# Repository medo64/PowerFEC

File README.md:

Power Framework Expansion Card
==============================

Non-isolated 5V output with a 500 mA current limit.

## Pinout

To connect to this board, one has to use a 2-pin JST XH connector. The following
table represents the pinout, pin 1 being on the left as looking into the
expansion card.

| # | Ref   | Description                     |
|--:|:-----:|---------------------------------|
| 1 | GND   | Ground connection               |
| 2 | 5V    | Positive voltage                |

## LEDs

Left LED signals if input is powered. It is expected to be on at all times.

Right LED signals if output is powered and there are no faults. It will turn off
if there is an over-current state (typically at around `525 mA`).

## Commands

Each char is a separate command. If it is recognized, output will be tilde
character (`~`), original command, and `CR``LF`.

| Char | Description                                                   |
|------|---------------------------------------------------------------|
| `0`  | No smoothing for voltage and current                          |
| `1`  | Voltage and current read are smoothed over 2 readings         |
| `2`  | Voltage and current read are smoothed over 4 readings         |
| `3`  | Voltage and current read are smoothed over 8 readings         |
| `4`  | Voltage and current read are smoothed over 16 readings        |
| `5`  | Voltage and current read are smoothed over 32 readings        |
| `6`  | Voltage and current read are smoothed over 64 readings        |
| `7`  | Voltage and current read are smoothed over 128 readings       |
| `8`  | Voltage and current read are smoothed over 256 readings       |
| `9`  | Voltage and current read are smoothed over 512 readings       |
| `d`  | Disable output                                                |
| `D`  | Disable output and allow saving for startup                   |
| `e`  | Enable output                                                 |
| `E`  | Enable output and allow saving for startup                    |
| `S`  | Saves current settings                                        |

Any command state that can be saved permanently (e.g. `E`) needs to be followed
by `S` command in order to be saved.

---
*You can check my blog and other projects at [www.medo64.com](https://www.medo64.com/electronics/).*

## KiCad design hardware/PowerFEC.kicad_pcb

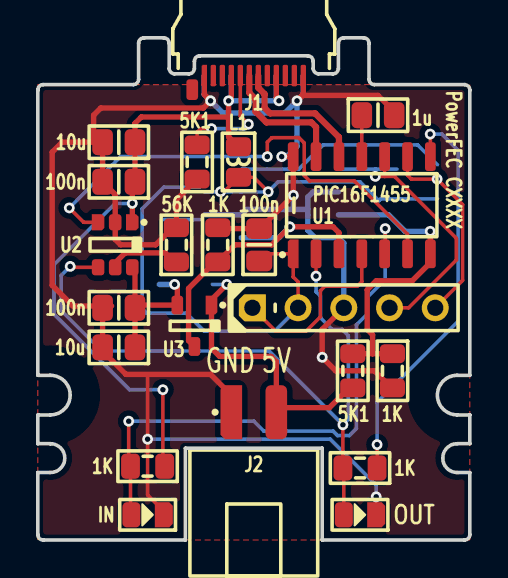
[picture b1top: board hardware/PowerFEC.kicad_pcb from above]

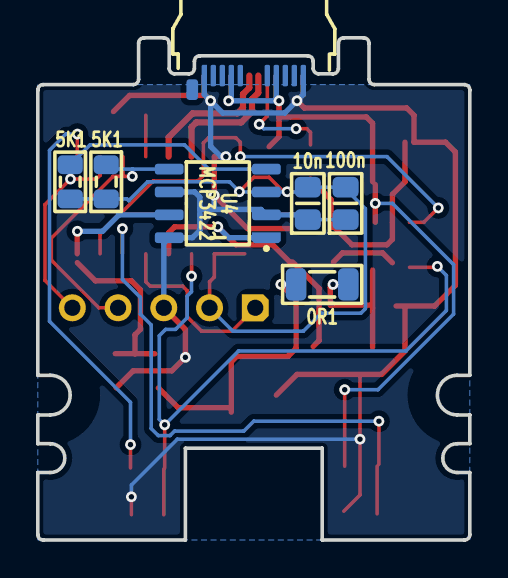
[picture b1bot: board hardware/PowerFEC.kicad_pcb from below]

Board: 2 copper layers, 24.0 x 27.9 mm, 28 parts (6 on the bottom side), 19 nets.

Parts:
C1: 10n; C (0805)
C2, C3, C4, C5: 100n; C (0805)
C6: 1u; C (0805)
C7, C8: 10u; C (0805)
DS1: IN; DS (0805)
DS2: OUT; DS (0805)
ICSP: Microchip PIC; ICSP PIC Pogo (5w)
J1: 105444-0001; J USB C 3.2 Edge (24w)
J2: B2B-XH-A; J JST XH Edge [POWER] (2w)
L1: 1u; L (0805)
R1: 0R1; R (1206)
R2, R3, R4, R5: 1K; R (0805)
R6, R7, R8, R9: 5K1; R (0805)
R10: 56K; R (0805)
U1: PIC16F1455; U Micro [PIC16F1455] (SOIC-14)
U2: AP22652; U LoadSwitch Adjustable [AP22652AW6-7] (SOT23-6)
U3: ZXCT1009; U Current Monitor [ZXCT1009] (SOT23-3)
U4: MCP3422; U ADC 18bit 2ch [MCP3422] (SOIC-8)

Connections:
5V: C1.1, C4.1, C5.1, ICSP.2, L1.2, R8.1, R9.1, U1.1, U4.3
A_CC: J1.A5, R6.2
GND: C1.2, C2.2, C3.2, C4.2, C5.2, C6.2, C7.2, C8.2, DS1.1, DS2.1, ICSP.3, J1.A1, J1.A12, J1.B01, J1.B12, J2.1, R2.2, R5.2, R6.1, R10.2, U1.14, U2.2, U4.2, U4.6, U4.8
ICSP_CLK/SDA: ICSP.5, R9.2, U1.9, U4.4
ICSP_DAT/SCL: ICSP.4, R8.2, U1.10, U4.5
ICSP_VPP: ICSP.1, U1.4
ILIM: R10.1, U2.5
Iadc: R2.1, U1.3, U3.3, U4.1
LED_IN: DS1.2, R3.2, U1.5
LED_OUT_HIGH: R4.1, U1.8
POWER_EN: U1.6, U2.3
POWER_FAULT: DS2.2, R4.2, U1.2, U2.4
USB_DM: J1.A7, U1.12
USB_DP: J1.A6, U1.13
V33: C6.1, U1.11
Vadc: R5.1, R7.2, U1.7, U4.7
Vin: C2.1, C7.1, J1.A4, J1.A9, J1.B04, J1.B09, L1.1, R3.1, U2.1
Vout: J2.2, R1.2, R7.1, U3.1
Vsw: C3.1, C8.1, R1.1, U2.6, U3.2

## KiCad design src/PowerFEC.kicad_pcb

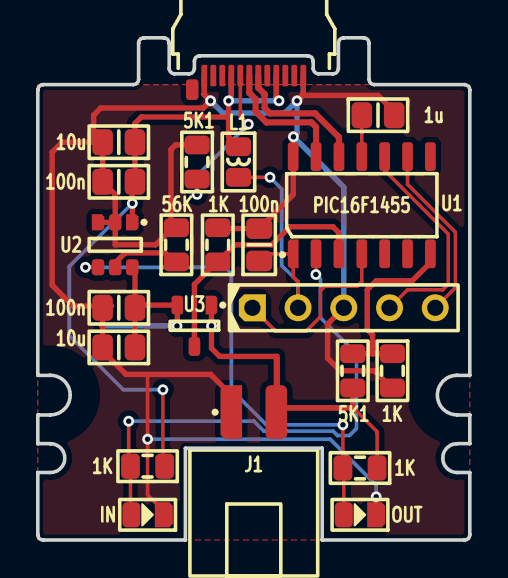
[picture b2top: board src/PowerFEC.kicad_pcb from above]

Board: 2 copper layers, 24.0 x 27.9 mm, 23 parts (1 on the bottom side), 17 nets.

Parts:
C1, C2, C3: 100n; C (0805)
C4: 1u; C (0805)
C5, C6: 10u; C (0805)
DS1: IN; DS (0805)
DS2: OUT; DS (0805)
ICSP: Microchip PIC; ICSP PIC Pogo (5w)
J1: B2B-XH-A; J JST XH Edge [POWER] (2w)
L1: 1u; L (0805)
P1: 105444-0001; P USB C 3.2 Edge (24w)
R1: 0R1; R (2512)
R2, R3, R4, R4#2: 1K; R (0805)
R5, R6: 5K1; R (0805)
R7: 56K; R (0805)
U1: PIC16F1455; U Micro PIC16F1455 (SOIC-14)
U2: AP22652; U CurrentLimiter AP22652 (SOT26)
U3: ZXCT1009; U CurrentSense ZXCT1009 (SOT23-3)

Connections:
5V: C3.1, ICSP.2, L1.2, U1.1
A_CC: P1.A5, R6.2
GND: C1.2, C2.2, C3.2, C4.2, C5.2, C6.2, DS1.1, DS2.1, ICSP.3, J1.1, P1.A1, P1.A12, P1.B01, P1.B12, R2.2, R4#2.2, R6.1, R7.2, U1.14, U2.2, U2.3
ICSP_CLK: ICSP.5, U1.9
ICSP_DAT: ICSP.4, U1.10
ICSP_VPP: ICSP.1, U1.4
ILIM: R7.1, U2.5
Iadc: R2.1, U1.3, U3.3
LED_IN: DS1.2, R3.2, U1.2
LED_OUT: DS2.2, R4.2, U2.4
USB_DM: P1.A7, U1.12
USB_DP: P1.A6, U1.13
V33: C4.1, U1.11
Vadc: R4#2.1, R5.2, U1.7
Vin: C1.1, C5.1, L1.1, P1.A4, P1.A9, P1.B04, P1.B09, R3.1, U2.1
Vout: J1.2, R1.2, R4.1, R5.1, U3.1
Vsw: C2.1, C6.1, R1.1, U2.6, U3.2

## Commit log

2023-12-30 Refactored to allow usage of PIC
2023-12-30 Refactoring copper pours
2023-12-30 Minor trace movements
2023-12-30 Added soldermask expand
2024-01-31 Moved LEDs
2024-02-04 Fixed current sense IC part number
2024-02-15 Moved hardware directory
2024-02-15 Initial firmware
2024-02-15 Added POWER_EN line
2024-02-15 Moved LED pin to allow for FAULT check (later)
2024-02-15 Added fault check pin
2024-02-15 Added fault checking
2024-02-16 Shorted moving average interval
2024-02-17 Added option to control out LED by PIC (in addition to FAULT)
2024-02-17 Adjusting LEDs a bit
2024-02-17 Added control of the right LED
2024-02-19 Updated USB edge connector designator
2024-02-24 more averaging
2024-02-24 Fix fault detection
2024-02-24 Renaming connectors
2024-02-24 Added ticket debug
2024-02-25 Smoothing is stored in settings
2024-02-25 Option to save smoothing state
2024-02-25 Added enable and disable setting
2024-02-25 Added option whether to have output enabled or disabled by default
2024-04-11 Added optional 18-bit ADC support
2024-04-11 Changed ADC to MCP3422
2024-04-11 Added 10nF capacitor
2024-04-11 Replaced current sense resistor with smaller one
2024-04-15 Fixed port typo
2024-04-15 Don't mark disabled device as faulted
2024-04-15 Bumped default revision to B
2024-04-15 Updated Pickit
2024-04-15 Fixed LED definitions (board B)
2024-04-15 Adjusted LED blinking on startup
2024-04-15 Auto-calibrate zero-offset for current
2024-04-15 Fixed smooting for zero values
2024-04-15 Adjusted current factor a bit
2024-04-15 Changed how flags are handled in settings
2024-04-18 Added output labels
2024-04-18 Refactoring a bit
2024-04-28 Upgraded to KiCAD 8
2024-05-11 Updated connector
2024-06-01 Fixed part number for PIC
2024-06-02 Fixed refdes
